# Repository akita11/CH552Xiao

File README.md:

# CH552Xiao

[WCH(南京沁恒微电子股份有限公司)](http://wch-ic.com/)の8ビットマイコン[CH552](http://wch-ic.com/products/CH552.html)を使った、Seeeduino Xiao型のマイコンボードです。
主な特徴は以下のとおりです。

- Seeeduino Xiao型
- [ArduinoIDEなどでプログラム開発が可能](https://qiita.com/akita11/items/d7baed4ca3c06e292637)
- USBペリフェラル（キーボードやUSBメモリなど）として動作可能
- USB Type-Cコネクタ

またSeeeduino Xiaoとは、以下のような違いがあります。
- 一部ピンの機能が異なる
- +5V端子に、外部電源から+5Vを供給可能（内部にレギュレータはないので、+5Vを超える電圧は不可）
- +3.3V出力の電流供給能力は100mA程度（CH552内蔵レギュレータの性能）
- **Seeeduino Xiaoとは+3.3Vと+5Vのピン配置が逆**（Seeeduino Xiao用拡張ボードを利用する場合などは注意してください）

## ピン配置

基板上の"LED"（オレンジ）はP3.0で駆動できます。

※ピン配置を変更した[CH552Xiao2](https://github.com/akita11/CH552Xiao2)もあわせて参照してください。

## Author

Junichi Akita (@akita11) / akita@ifdl.jp

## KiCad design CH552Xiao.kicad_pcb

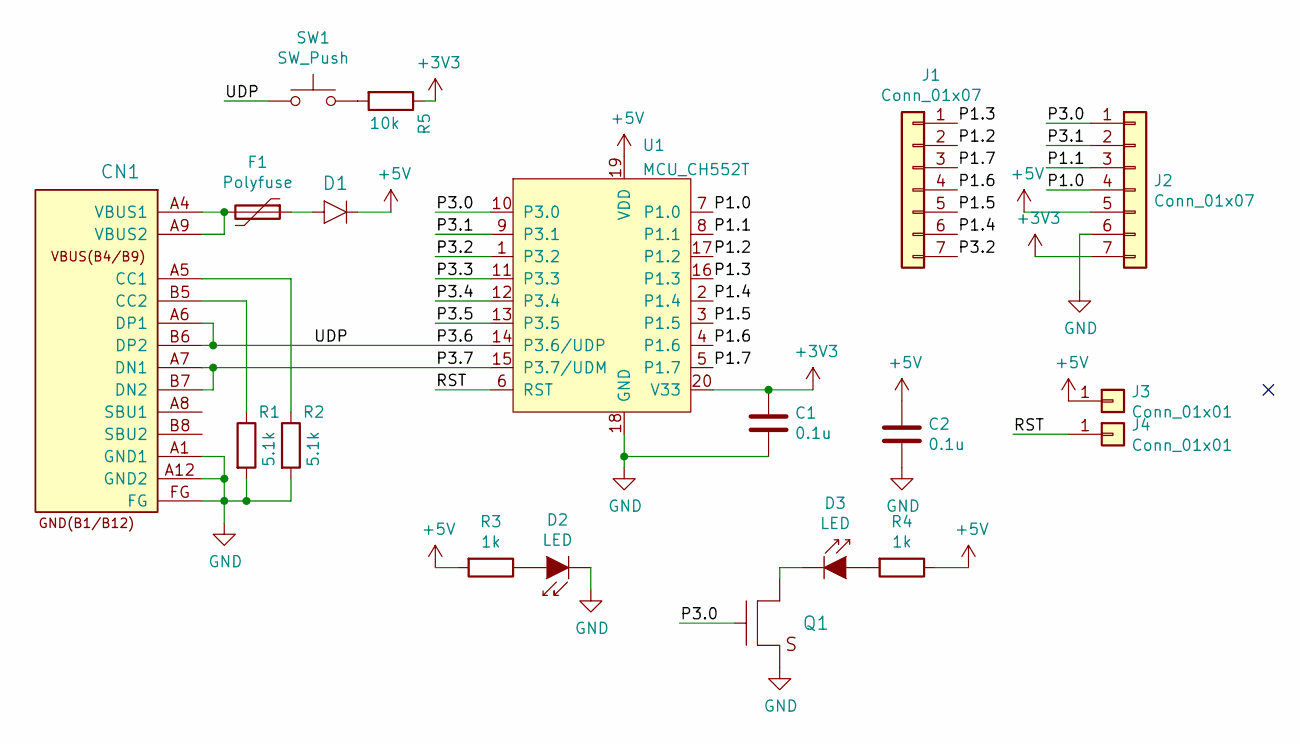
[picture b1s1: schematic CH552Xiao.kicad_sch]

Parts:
C1, C2: 0.1u; C_0603_1608Metric
CN1: CON_USB-C-16; USB-C_16P_TH
D1: DIODE; D_SOD123FL
D2, D3: LED; LED_0603_1608Metric
F1: Polyfuse; R_1210_3225Metric
J1, J2: Conn_01x07; Socker2.54mm_7p_OvalPad
J3, J4: Conn_01x01; Pad_SMD1.6mm
Q1: TR_NMOS_IRLML6344; SOT-23
R1, R2: 5.1k; R_0603_1608Metric
R3, R4: 1k; R_0603_1608Metric
R5: 10k; R_0603_1608Metric
SW1: SW_Push; SW_Push_SPST_NO_Alps_SKRK
U1: MCU_CH552T; TSSOP-20_4.4x6.5mm_P0.65mm

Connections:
+3V3: C1.1, J2.7, J2.-, R5.1, U1.20 (V33)
+5V: C2.1, D1.K, J2.5, J3.1, R3.2, R4.1, U1.19 (VDD)
/P1.0: J2.4, U1.7 (P1.0)
/P1.1: J2.3, U1.8 (P1.1)
/P1.2: J1.2, U1.17 (P1.2)
/P1.3: J1.1, U1.16 (P1.3)
/P1.4: J1.6, U1.2 (P1.4)
/P1.5: J1.5, U1.3 (P1.5)
/P1.6: J1.4, U1.4 (P1.6)
/P1.7: J1.3, U1.5 (P1.7)
/P3.0: J2.1, Q1.1 (G), U1.10 (P3.0)
/P3.1: J2.2, U1.9 (P3.1)
/P3.2: J1.7, U1.1 (P3.2)
/P3.3: U1.11 (P3.3)
/P3.4: U1.12 (P3.4)
/P3.5: U1.13 (P3.5)
/P3.6: CN1.A6 (DP1), CN1.B6 (DP2), SW1.1, U1.14 (P3.6/UDP)
/P3.7: CN1.A7 (DN1), CN1.B7 (DN2), U1.15 (P3.7/UDM)
/RST: J4.1, U1.6 (RST)
GND: C1.2, C2.2, CN1.A1 (GND1), CN1.A12 (GND2), CN1.FG, D2.1 (K), J2.6, Q1.2 (S), R1.2, R2.2, U1.18 (GND)
unnamed: CN1.A4 (VBUS1), CN1.A9 (VBUS2), F1.2
unnamed: CN1.A5 (CC1), R2.1
unnamed: CN1.B5 (CC2), R1.1
unnamed: D1.A, F1.1
unnamed: D2.2 (A), R3.1
unnamed: D3.1 (K), Q1.3 (D)
unnamed: D3.2 (A), R4.2
unnamed: R5.2, SW1.2

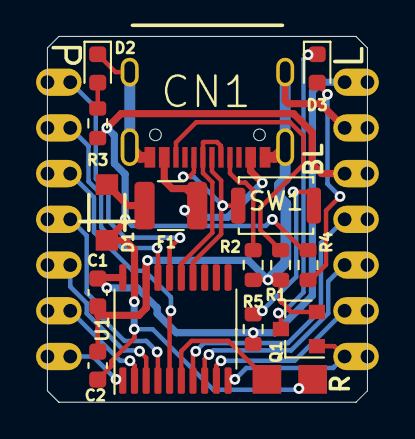
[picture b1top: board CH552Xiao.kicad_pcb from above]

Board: 2 copper layers, 17.8 x 20.3 mm, 19 parts (0 on the bottom side), 25 nets.

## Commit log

2021-12-31 remove vias under USB connector
2022-01-19 KiCAD6、CH552T
2022-01-19 add pin map
2022-01-19 pin map
2022-01-20 resize pin map image
2022-01-20 外部電源について追記
2022-01-26 add image
2022-01-26 add LED pin
2022-01-26 pin map correct
2022-01-26 電源ピンについての注意を追記
2022-01-28 +3.3V出力電流について追記
2022-01-28 add schematic
2022-03-03 CH552Xiao2について追記
